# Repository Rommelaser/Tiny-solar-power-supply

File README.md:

# Tiny-solar-power-supply
Práctica  de Kicad utilizando diseño de revista elektor

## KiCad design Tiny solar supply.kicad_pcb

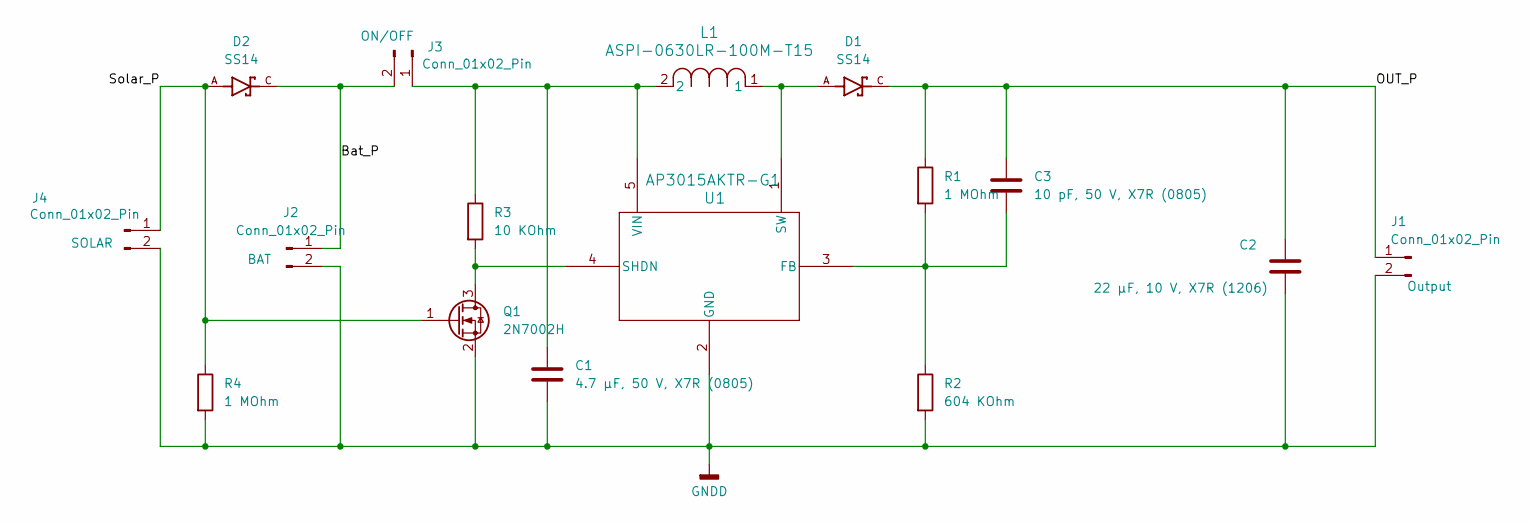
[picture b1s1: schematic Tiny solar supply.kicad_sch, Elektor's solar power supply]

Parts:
C1: 4.7 µF, 50 V, X7R (0805); C_0805_2012Metric
C2: 22 µF, 10 V, X7R (1206); C_1206_3216Metric
C3: 10 pF, 50 V, X7R (0805); C_0805_2012Metric
D1, D2: SS14; DIOM4325X250N; PARTREV O2102
J1, J2, J3: Conn_01x02_Pin; PinHeader_1x02_P2.54mm_Vertical
J4: Conn_01x02_Pin; PinHeader_1x02_P2.54mm_Horizontal
L1: ASPI-0630LR-100M-T15; IND_ASPI-0630LR_ABR
Q1: 2N7002H; SOT-23
R1, R4: 1 MOhm; R_0805_2012Metric
R2: 604 KOhm; R_0805_2012Metric
R3: 10 KOhm; R_0805_2012Metric
U1: AP3015AKTR-G1; SOT23-5_1P55X2P9_DIO

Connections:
/Bat_P: D2.C, J2.1, J3.2
/OUT_P: C2.1, C3.1, D1.C, J1.1, R1.1
/Solar_P: D2.A, J4.1, Q1.1 (G), R4.1
GNDD: C1.2, C2.2, J1.2, J2.2, J4.2, Q1.2 (S), R2.2, R4.2, U1.2 (GND)
unnamed: C1.1, J3.1, L1.2, R3.1, U1.5 (VIN)
unnamed: Q1.3 (D), R3.2, U1.4 (SHDN)
unnamed: C3.2, R1.2, R2.1, U1.3 (FB)
unnamed: D1.A, L1.1, U1.1 (SW)

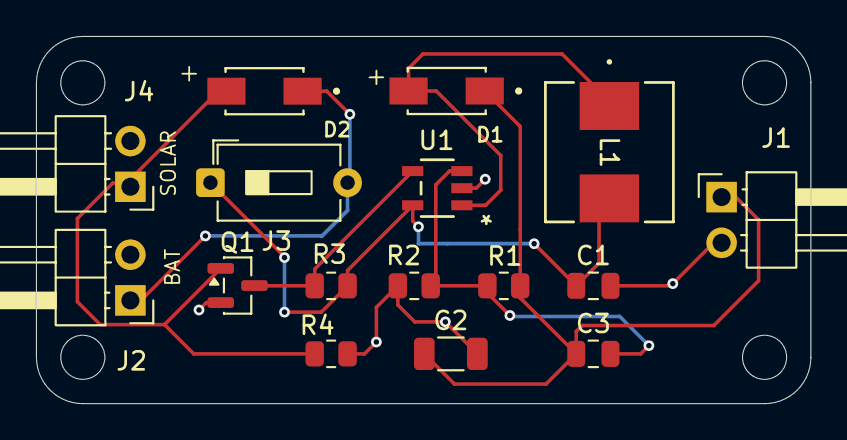
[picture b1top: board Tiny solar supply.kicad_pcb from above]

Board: 2 copper layers, 43.0 x 20.4 mm, 16 parts (0 on the bottom side), 8 nets.

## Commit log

2026-02-21 se agregaron los archivos del proyecto y se configuro el .gitignore
